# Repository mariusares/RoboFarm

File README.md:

RoboFarm Greenhouse Automation, Irrigation Automation, and Poultry Farm Automation with Arduino and Raspberry Pi 

Long story short, a few years ago (in 2017 i think), a guy criticized the graphical interface.

At that moment I realized that he has to be a part of the team. 

So the GUI look and feel by Alex Hodorogea 

The PHP GUI (HTML folder) is in the Romanian language. Would be translated at some stage (too busy nowadays).

The sql file contains the MySQL/MariaDB SQL database structure

The default username is admin password admin 

For those who want more than a test, the PCB Layout is available for printing under CeresOne folder.

Initially, I gave up the name RoboFarm, because so many projects with this name. Feel free to name it as you pleased.

Under CeresOne/Resources you can see the pieces of the schematics, and how the power source and PCB board were designed. 

The project can work with a radio module with some software modifications.

Feel free to use it as you pleased. 

First version based on Arduino Mega with Google Docs logs  in production on 2015 :

https://www.youtube.com/watch?v=YMtiKbJgd4w&t=180s

First RaspberryPi + Arduino (Arduino is the sensor hub to feed the RPi data string) + first Web GUI:

https://www.youtube.com/watch?v=SSzuTgg7uxc&t=3s

png folder contains the new (actual) GUI version.

The system is designed to reduce farming costs and effort.

I hope that there would be a very happy farmer. 

The system was designed to help my uncle and every farmer that might need a bit of "help".

RoboFarm can be the best employee, he can ventilate the farm at 5AM if necessary.

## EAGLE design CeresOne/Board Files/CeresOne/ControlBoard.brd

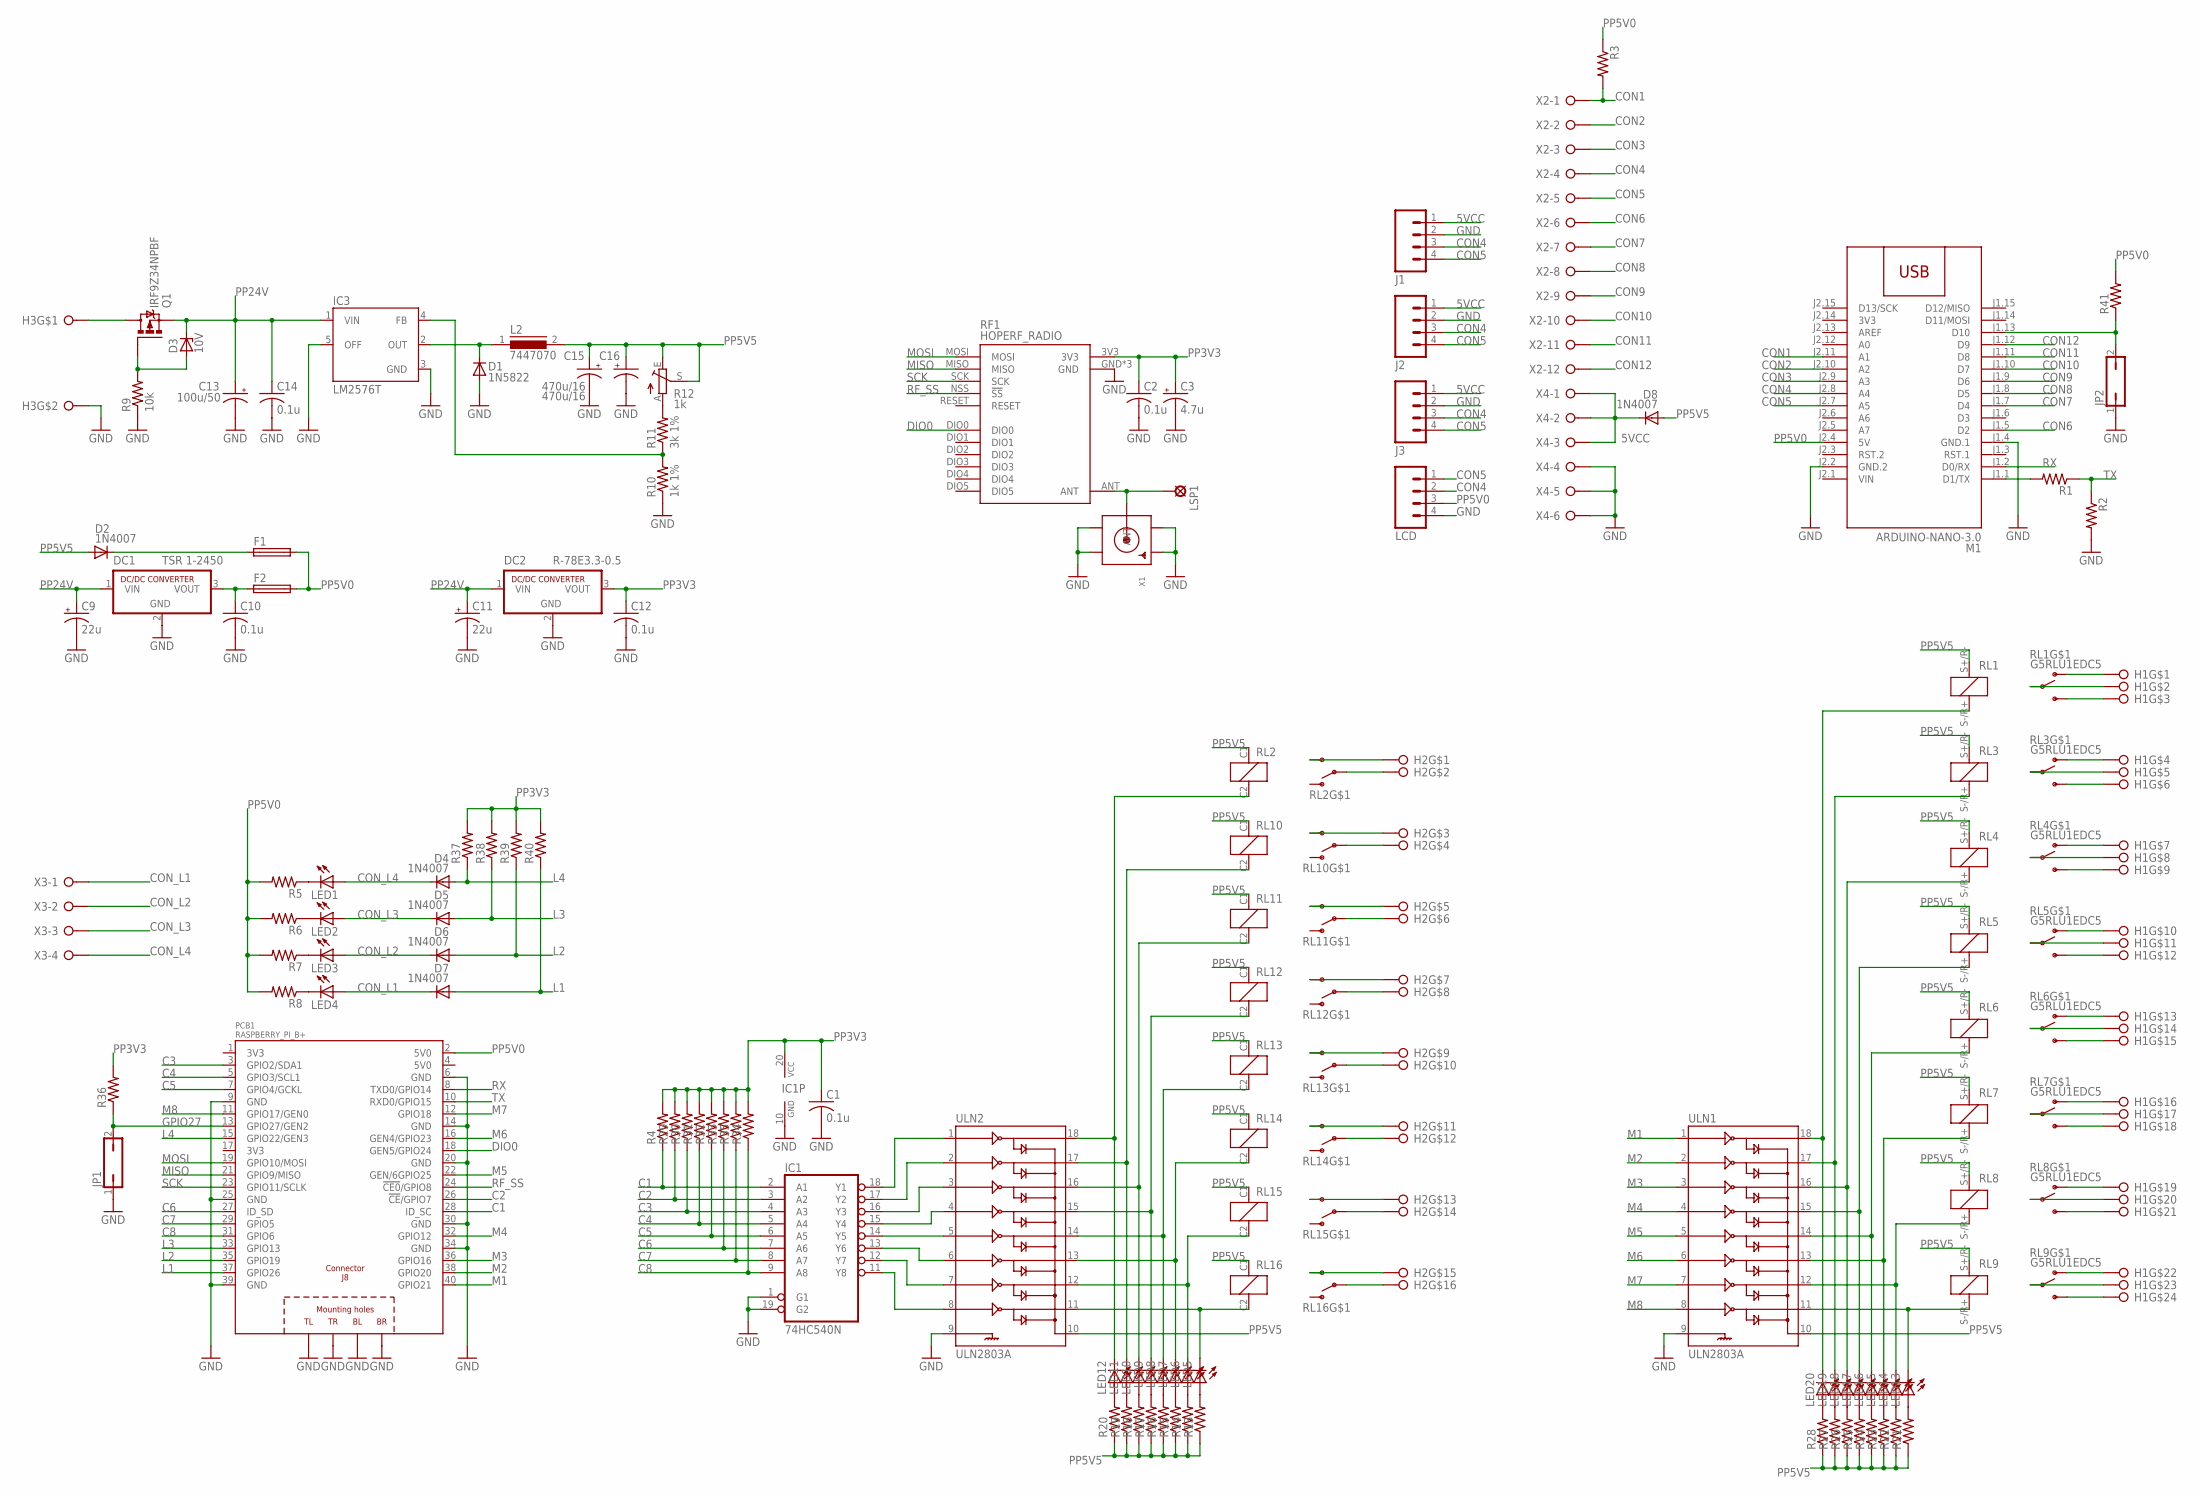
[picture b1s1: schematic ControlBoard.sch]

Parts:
C1, C2, C10, C12, C14: 0.1u; C050-030X075
C3: 4.7u; E2,5-5
C9, C11: 22u; E2,5-6
C13: 100u/50; E5-10,5
C15, C16: 470u/16; E5-10,5
D1: 1N5822; DO201-15
D2, D4, D5, D6, D7, D8: 1N4007; DO41-10
D3: 10V; DO34Z7
DC1: TSR 1-2450; SIP3
DC2: R-78E3.3-0.5; SIP3
F1, F2: TE5
H1: 24X1(0.300)CONN; 24/7.62CONN
H2: 16X1(0.300)CONN; 16/7.62CONN
H3: 2X1(0.300)CONN; 2/7.62CONN
IC1: 74HC540N; DIL20
IC3: LM2576T; TO220-5
J1, J2, J3: M04PTH; 1X04
JP1, JP2: JP1Q; JP1
L2: 7447070; SFT830D
LCD: M04PTH; 1X04
LED1, LED2, LED3, LED4, LED5, LED6, LED7, LED8, LED9, LED10, LED11, LED12, LED13, LED14, LED15, LED16, LED17, LED18, LED19, LED20: LED3MM
LSP1: LSP11
M1: ARDUINO-NANO-3.0
PCB1: RASPBERRY_PI_B+
Q1: IRF9Z34NPBF; TO220BV
R1, R2, R3, R4, R21, R22, R23, R24, R25, R26, R27, R28, R29, R30, R31, R32, R33, R34, R35, R36, R37, R38, R39, R40, R41: R-US_0204/7; 0204/7
R5, R6, R7, R8, R13, R14, R15, R16, R17, R18, R19, R20: R-US_0207/2V; 0207/2V
R9: 10k; 0204/7
R10: 1k 1%; 0207/2V
R11: 3k 1%; 0207/2V
R12: 1k; RJ9W
RF1: HOPERF_RADIO; RADIO_MODULE
RL1, RL3, RL4, RL5, RL6, RL7, RL8, RL9: G5RLU1EDC5; DOUBLE_RELAY
RL2, RL10, RL11, RL12, RL13, RL14, RL15, RL16: OMIH-SS-105LM,300
ULN1, ULN2: ULN2803A; DIL18
X1: SMACONNECTOR; SMA90_DIP
X2: W237-12P
X3: W237-04P; W237-4P
X4: W237-06P; W237-6P

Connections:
3V3: M1.J2.14 (3V3)
5VCC: D8.C, J1.1, J2.1, J3.1, X4.1, X4.2, X4.3
C1: IC1.2 (A1), PCB1.28 (ID_SC), R4.1
C2: IC1.3 (A2), PCB1.26 (!CE!/GPIO7), R29.1
C3: IC1.4 (A3), PCB1.3 (GPIO2/SDA1), R30.1
C4: IC1.5 (A4), PCB1.5 (GPIO3/SCL1), R31.1
C5: IC1.6 (A5), PCB1.7 (GPIO4/GCKL), R32.1
C6: IC1.7 (A6), PCB1.27 (ID_SD), R33.1
C7: IC1.8 (A7), PCB1.29 (GPIO5), R35.1
C8: IC1.9 (A8), PCB1.31 (GPIO6), R34.1
CON1: M1.J2.11 (A1), R3.2, X2.1
CON2: M1.J2.10 (A2), X2.2
CON3: M1.J2.9 (A3), X2.3
CON4: J1.3, J2.3, J3.3, LCD.2, M1.J2.8 (A4), X2.4
CON5: J1.4, J2.4, J3.4, LCD.1, M1.J2.7 (A5), X2.5
CON6: M1.J1.5 (D2), X2.6
CON7: M1.J1.7 (D4), X2.7
CON8: M1.J1.8 (D5), X2.8
CON9: M1.J1.9 (D6), X2.9
CON10: M1.J1.10 (D7), X2.10
CON11: M1.J1.11 (D8), X2.11
CON12: M1.J1.12 (D9), X2.12
CON_L1: D7.C, LED4.A, X3.1
CON_L2: D6.C, LED3.A, X3.2
CON_L3: D5.C, LED2.A, X3.3
CON_L4: D4.C, LED1.A, X3.4
DIO0: PCB1.18 (GEN5/GPIO24), RF1.DIO0
GND: C1.2, C2.2, C3.-, C9.-, C10.2, C11.-, C12.2, C13.-, C14.2, C15.-, C16.-, D1.A, DC1.2 (GND), DC2.2 (GND), H3.P$2, IC1.1 (G1), IC1.10 (GND), IC1.19 (G2), IC3.3 (GND), IC3.5 (OFF), J1.2, J2.2, J3.2, JP1.1, JP2.1, LCD.4, M1.J1.4 (GND.1), M1.J2.2 (GND.2), PCB1.6 (GND), PCB1.9 (GND), PCB1.14 (GND), PCB1.20 (GND), PCB1.25 (GND), PCB1.30 (GND), PCB1.34 (GND), PCB1.39 (GND), PCB1.PE_BL (BL), PCB1.PE_BR (BR), PCB1.PE_TL (TL), PCB1.PE_TR (TR), R2.2, R9.1, R10.1, RF1.GND, RF1.GND1 (GND), RF1.GND2 (GND), ULN1.9, ULN2.9, X1.GND1, X1.GND2, X1.GND3, X1.GND4, X4.4, X4.5, X4.6
GPIO27: JP1.2, PCB1.13 (GPIO27/GEN2), R36.1
L1: D7.A, PCB1.37 (GPIO26), R40.1
L2: D6.A, PCB1.35 (GPIO19), R39.1
L3: D5.A, PCB1.33 (GPIO13), R38.1
L4: D4.A, PCB1.15 (GPIO22/GEN3), R37.1
M1: PCB1.40 (GPIO21), ULN1.1
M2: PCB1.38 (GPIO20), ULN1.2
M3: PCB1.36 (GPIO16), ULN1.3
M4: PCB1.32 (GPIO12), ULN1.4
M5: PCB1.22 (GEN/6GPIO25), ULN1.5
M6: PCB1.16 (GEN4/GPIO23), ULN1.6
M7: PCB1.12 (GPIO18), ULN1.7
M8: PCB1.11 (GPIO17/GEN0), ULN1.8
MISO: PCB1.21 (GPIO9/MISO), RF1.MISO
MOSI: PCB1.19 (GPIO10/MOSI), RF1.MOSI
unnamed: H1.1, RL1.NC1 (NC), RL1.NC2 (NC), RL1.NC3 (NC)
unnamed: H1.3, RL1.NO1 (NO), RL1.NO2 (NO), RL1.NO3 (NO)
unnamed: H1.4, RL3.NC1 (NC), RL3.NC2 (NC), RL3.NC3 (NC)
unnamed: H1.6, RL3.NO1 (NO), RL3.NO2 (NO), RL3.NO3 (NO)
unnamed: H1.7, RL4.NC1 (NC), RL4.NC2 (NC), RL4.NC3 (NC)
unnamed: H1.9, RL4.NO1 (NO), RL4.NO2 (NO), RL4.NO3 (NO)
unnamed: H1.10, RL5.NC1 (NC), RL5.NC2 (NC), RL5.NC3 (NC)
unnamed: H1.12, RL5.NO1 (NO), RL5.NO2 (NO), RL5.NO3 (NO)
unnamed: H1.13, RL6.NC1 (NC), RL6.NC2 (NC), RL6.NC3 (NC)
unnamed: H1.15, RL6.NO1 (NO), RL6.NO2 (NO), RL6.NO3 (NO)
unnamed: H1.16, RL7.NC1 (NC), RL7.NC2 (NC), RL7.NC3 (NC)
unnamed: H1.18, RL7.NO1 (NO), RL7.NO2 (NO), RL7.NO3 (NO)
unnamed: H1.19, RL8.NC1 (NC), RL8.NC2 (NC), RL8.NC3 (NC)
unnamed: H1.21, RL8.NO1 (NO), RL8.NO2 (NO), RL8.NO3 (NO)
unnamed: H1.22, RL9.NC1 (NC), RL9.NC2 (NC), RL9.NC3 (NC)
unnamed: H1.24, RL9.NO1 (NO), RL9.NO2 (NO), RL9.NO3 (NO)
unnamed: H1.2, RL1.COM1 (COM), RL1.COM2 (COM)
unnamed: H1.5, RL3.COM1 (COM), RL3.COM2 (COM)
unnamed: H1.8, RL4.COM1 (COM), RL4.COM2 (COM)
unnamed: H1.11, RL5.COM1 (COM), RL5.COM2 (COM)
unnamed: H1.14, RL6.COM1 (COM), RL6.COM2 (COM)
unnamed: H1.17, RL7.COM1 (COM), RL7.COM2 (COM)
unnamed: H1.20, RL8.COM1 (COM), RL8.COM2 (COM)
unnamed: H1.23, RL9.COM1 (COM), RL9.COM2 (COM)
unnamed: H2.2, RL2.COM
unnamed: H2.4, RL10.COM
unnamed: H2.6, RL11.COM
unnamed: H2.8, RL12.COM
unnamed: H2.10, RL13.COM
unnamed: H2.12, RL14.COM
unnamed: H2.14, RL15.COM
unnamed: H2.16, RL16.COM
unnamed: H2.1, RL2.NO
unnamed: H2.3, RL10.NO
unnamed: H2.5, RL11.NO
unnamed: H2.7, RL12.NO
unnamed: H2.9, RL13.NO
unnamed: H2.11, RL14.NO
unnamed: H2.13, RL15.NO
unnamed: H2.15, RL16.NO
unnamed: LED13.K (C), RL9.S-/R+ (2), ULN1.11
unnamed: LED14.K (C), RL8.S-/R+ (2), ULN1.12
unnamed: LED15.K (C), RL7.S-/R+ (2), ULN1.13
unnamed: LED16.K (C), RL6.S-/R+ (2), ULN1.14
unnamed: LED17.K (C), RL5.S-/R+ (2), ULN1.15
unnamed: LED18.K (C), RL4.S-/R+ (2), ULN1.16
unnamed: LED19.K (C), RL3.S-/R+ (2), ULN1.17
unnamed: LED20.K (C), RL1.S-/R+ (2), ULN1.18
unnamed: LED12.K (C), RL2.C2 (2), ULN2.18
unnamed: LED11.K (C), RL10.C2 (2), ULN2.17
unnamed: LED10.K (C), RL11.C2 (2), ULN2.16
unnamed: LED9.K (C), RL12.C2 (2), ULN2.15
unnamed: LED8.K (C), RL13.C2 (2), ULN2.14
unnamed: LED7.K (C), RL14.C2 (2), ULN2.13
unnamed: LED6.K (C), RL15.C2 (2), ULN2.12
unnamed: LED5.K (C), RL16.C2 (2), ULN2.11
unnamed: IC1.11 (Y8), ULN2.8
unnamed: IC1.12 (Y7), ULN2.7
unnamed: IC1.13 (Y6), ULN2.6
unnamed: IC1.14 (Y5), ULN2.5
unnamed: IC1.15 (Y4), ULN2.4
unnamed: IC1.16 (Y3), ULN2.3
unnamed: IC1.17 (Y2), ULN2.2
unnamed: IC1.18 (Y1), ULN2.1
unnamed: LSP1.MP, RF1.ANT, X1.ANTENNA (ANT)
unnamed: M1.J1.1 (D1/TX), R1.2
unnamed: LED1.K (C), R5.1
unnamed: LED2.K (C), R6.1
unnamed: LED3.K (C), R7.1
unnamed: D3.A, Q1.G, R9.2
unnamed: IC3.4 (FB), R10.2, R11.1
unnamed: LED4.K (C), R8.1
unnamed: H3.P$1, Q1.D
unnamed: D2.C, F1.1
unnamed: C10.1, DC1.3 (VOUT), F2.1
unnamed: D1.C, IC3.2 (OUT), L2.1
unnamed: R11.2, R12.A
unnamed: LED5.A, R13.2
unnamed: LED6.A, R14.2
unnamed: LED7.A, R15.2
unnamed: LED8.A, R16.2
unnamed: LED9.A, R17.2
unnamed: LED10.A, R18.2
unnamed: LED11.A, R19.2
unnamed: LED12.A, R20.2
unnamed: LED13.A, R21.2
unnamed: LED14.A, R22.2
unnamed: LED15.A, R23.2
unnamed: LED16.A, R24.2
unnamed: LED17.A, R25.2
unnamed: LED18.A, R26.2
unnamed: LED19.A, R27.2
unnamed: LED20.A, R28.2
unnamed: JP2.2, M1.J1.13 (D10), R41.1
PP3V3: C1.1, C2.1, C3.+, C12.1, DC2.3 (VOUT), IC1.20 (VCC), R4.2, R29.2, R30.2, R31.2, R32.2, R33.2, R34.2, R35.2, R36.2, R37.2, R38.2, R39.2, R40.2, RF1.3V3
PP5V0: F1.2, F2.2, LCD.3, M1.J2.4 (5V), PCB1.2 (5V0), R3.1, R5.2, R6.2, R7.2, R8.2, R41.2
PP5V5: C15.+, C16.+, D2.A, D8.A, L2.2, R12.E, R12.S, R13.1, R14.1, R15.1, R16.1, R17.1, R18.1, R19.1, R20.1, R21.1, R22.1, R23.1, R24.1, R25.1, R26.1, R27.1, R28.1, RL1.S+/R- (1), RL2.C1 (1), RL3.S+/R- (1), RL4.S+/R- (1), RL5.S+/R- (1), RL6.S+/R- (1), RL7.S+/R- (1), RL8.S+/R- (1), RL9.S+/R- (1), RL10.C1 (1), RL11.C1 (1), RL12.C1 (1), RL13.C1 (1), RL14.C1 (1), RL15.C1 (1), RL16.C1 (1), ULN1.10, ULN2.10
PP24V: C9.+, C11.+, C13.+, C14.1, D3.C, DC1.1 (VIN), DC2.1 (VIN), IC3.1 (VIN), Q1.S
RF_SS: PCB1.24 (!CE0!/GPIO8), RF1.NSS (!SS)
RX: M1.J1.2 (D0/RX), PCB1.8 (TXD0/GPIO14)
SCK: PCB1.23 (GPIO11/SCLK), RF1.SCK
TX: PCB1.10 (RXD0/GPIO15), R1.1, R2.1
VIN: M1.J2.1 (VIN)

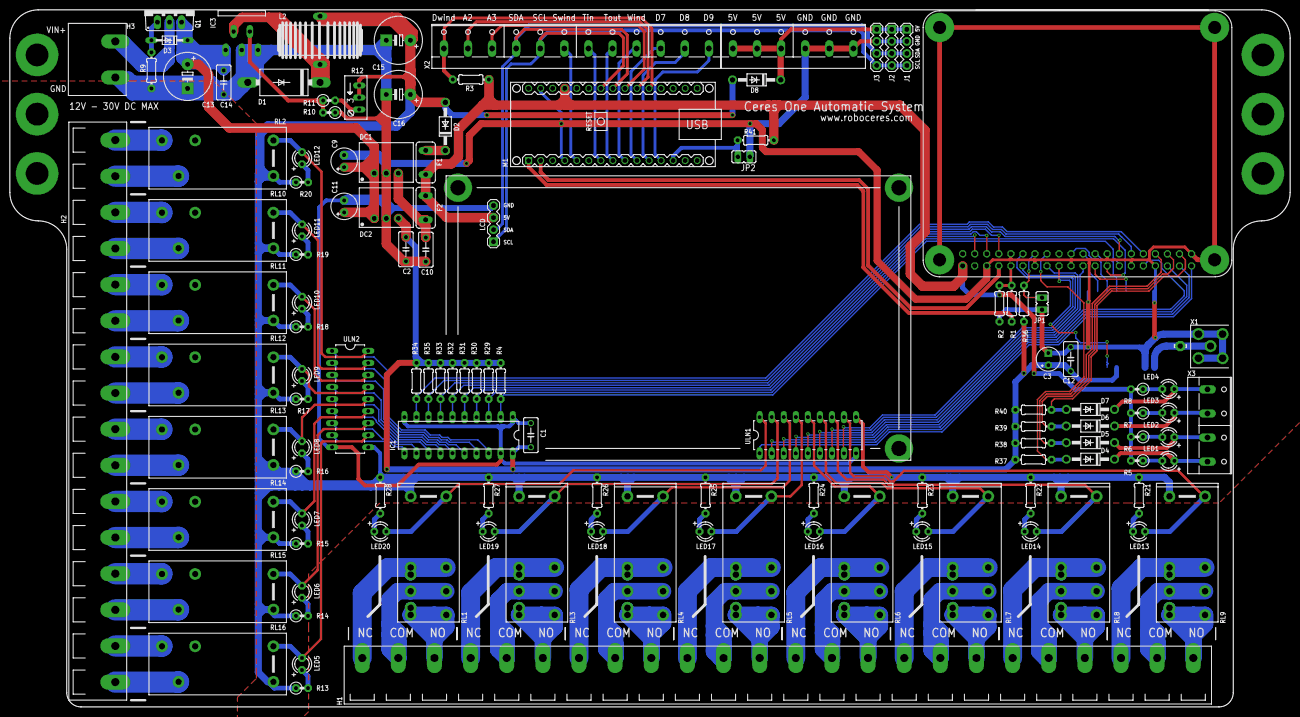
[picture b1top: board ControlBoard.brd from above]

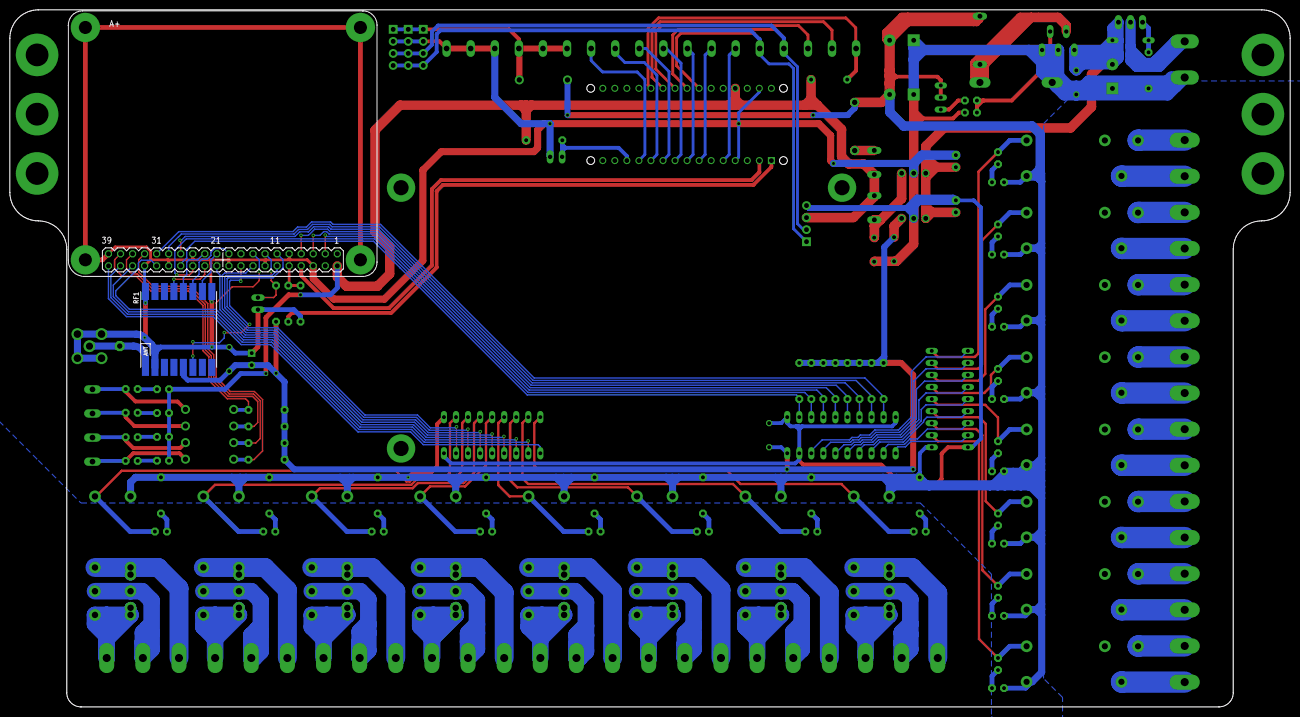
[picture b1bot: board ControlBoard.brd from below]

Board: 2 copper layers, 270.0 x 147.0 mm, 123 parts (2 on the bottom side), 144 nets.

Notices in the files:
parts and their libraries:
SparkFun-Connectors: Licensing: Creative Commons ShareAlike 4.0 International - https://creativecommons.org/licenses/by-sa/4.0
diy-modules: Released under the Creative Commons Attribution 4.0 International License: http://creativecommons.org/licenses/by/4.0
